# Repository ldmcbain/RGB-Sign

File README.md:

# RGB Sign
 RGB Wifi Sign Controller using ESP32-DevkitC-32E

This is an RGB Sign I created for our church.  It is an Arduino based design using a custom PCB I created to conrol three separate RGB strings.  I created the PCB using a two-sided copper board and a laser burner, but someone could just as easily send it out for build.

The Arduino is setup to create a WIFI captive portal which is used to control the three strands. Update the wifi settings in the arduino code prior to use.

Note that the PCB uses the ESP32-DevkitC-32E layout.  Other ESP32 variations may have incorrect dimensions or pinouts.

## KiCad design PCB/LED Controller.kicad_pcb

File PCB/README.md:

This PCB was created in KiCad v5.1.10

I generated the PCB using a standard 5W laser.  Here are my steps to do so if you are so inclined:

Like all things, follow these steps at your own risk.  This process involves toxic chemicals, soldering, etc and you must follow proper safety precautions if attempting.  If you are not comfortable with the equipment/process, don't do it.

**KiCad Design**
  Min Trace Width: 0.4mm
  Min Clearance: 0.25mm
  All Vias should be 2.5mm diameter and not placed under anything
  Use a ground flood plane on most surfaces (reduces required lasering)
  
**From within PCBNew**
  Plot out Top/Bottom Cu layers to PDF.  Utilize small drill holes, show cut edge on all layers
  
**Using GIMP**
1. Import PDF as high res (2400 dpi)
2. Auto Crop to content
3. Modify to fill in the outer edge so that it is all black (don't laser the edges)
4. Export as high res PNG

**Prepare the Board**
1. (optional) Sand the board lightly with 400 grit
2. Spray paint the board (both sides).  Make sure fully coated.  I used the cheap matte black spray at walmart.  Use two coats if needed.

**Lightburn Laser Control SW**
1. Import PNG into lightburn
2. Use Following settings for laser (this is what worked for me, modify as needed)
  a. 60% power
  b. speed: 3mm/s
  c. Bi-directional: Off
  d. Negative Image: On
  e. Overscanning: Off
  f. Line Interval: 0.1mm
  g. Passes: 1

**Burning and Post Clean up/Fabrication**
1. Position and Burn the Board (one side at a time..).  Note: you should be burning a Negative image on the board (areas in-between the copper).
2. Clean up board with scotch bright pad (and water).  Use a ultra fine tip marker to fix damaged areas if needed.
3. After both sides are burned, etch the board using ferric chloride solution.  This can be obtained from amazon.  USE GLOVES!!  There are several youtube videos showing how to do this if you are unfamiliar with the process.
4. Clean the board with water.  Inspect and re-etch if needed.
5. Use acetone or paint thinner to remove remaining paint from the board.
6. Clean board with alcohol (i use the 90% stuff at walmart)
7. Drill the holes.  I obtained very small drills from amazon for the purpose and used a drill press.  Use 0.8mm dia for vias.  They *should* be marked with small dots.  use the drill map to make sure you get all of them with the right size drills.
8. In some instances, I've found it helpful to pre-tin the board in certain locations.
9. Assemble the board.

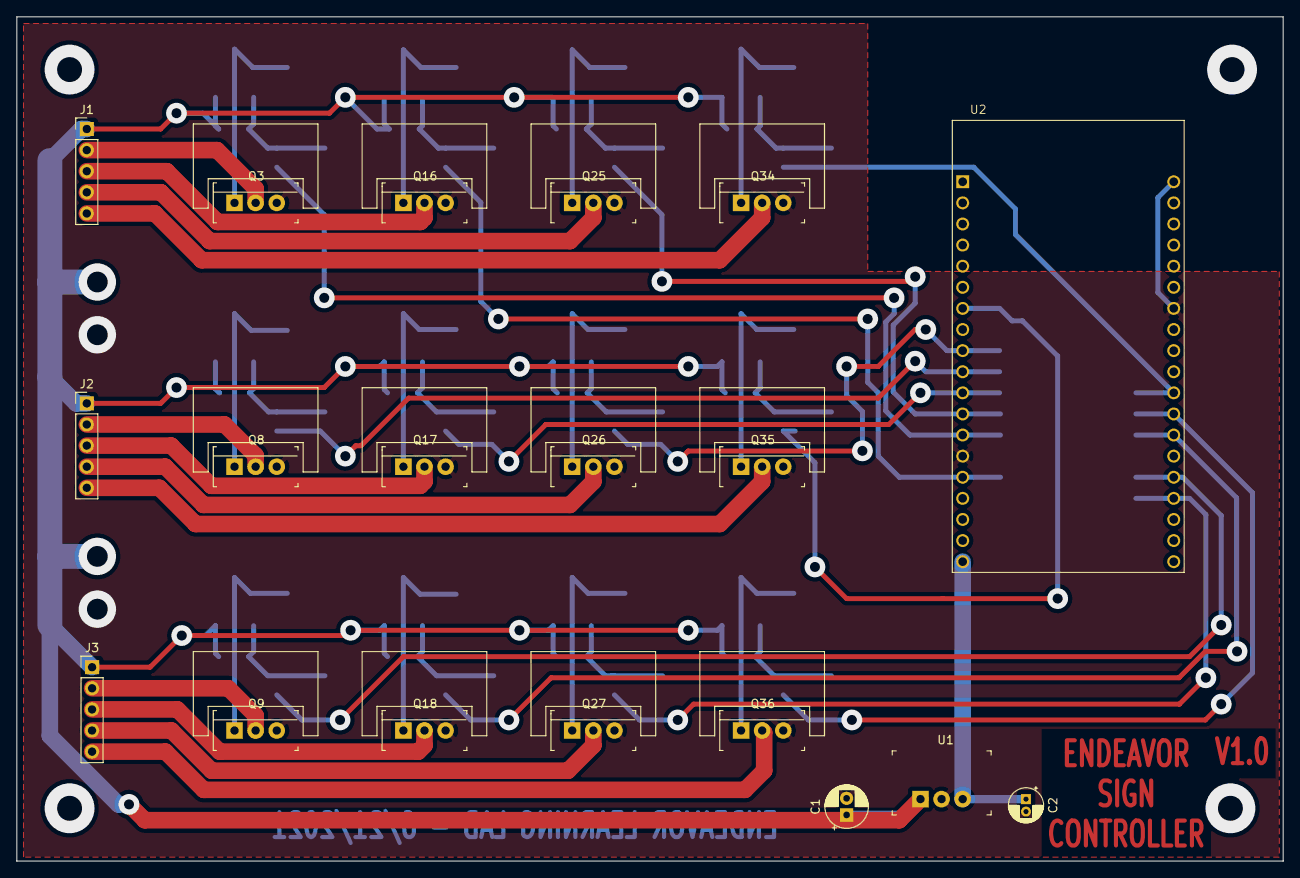
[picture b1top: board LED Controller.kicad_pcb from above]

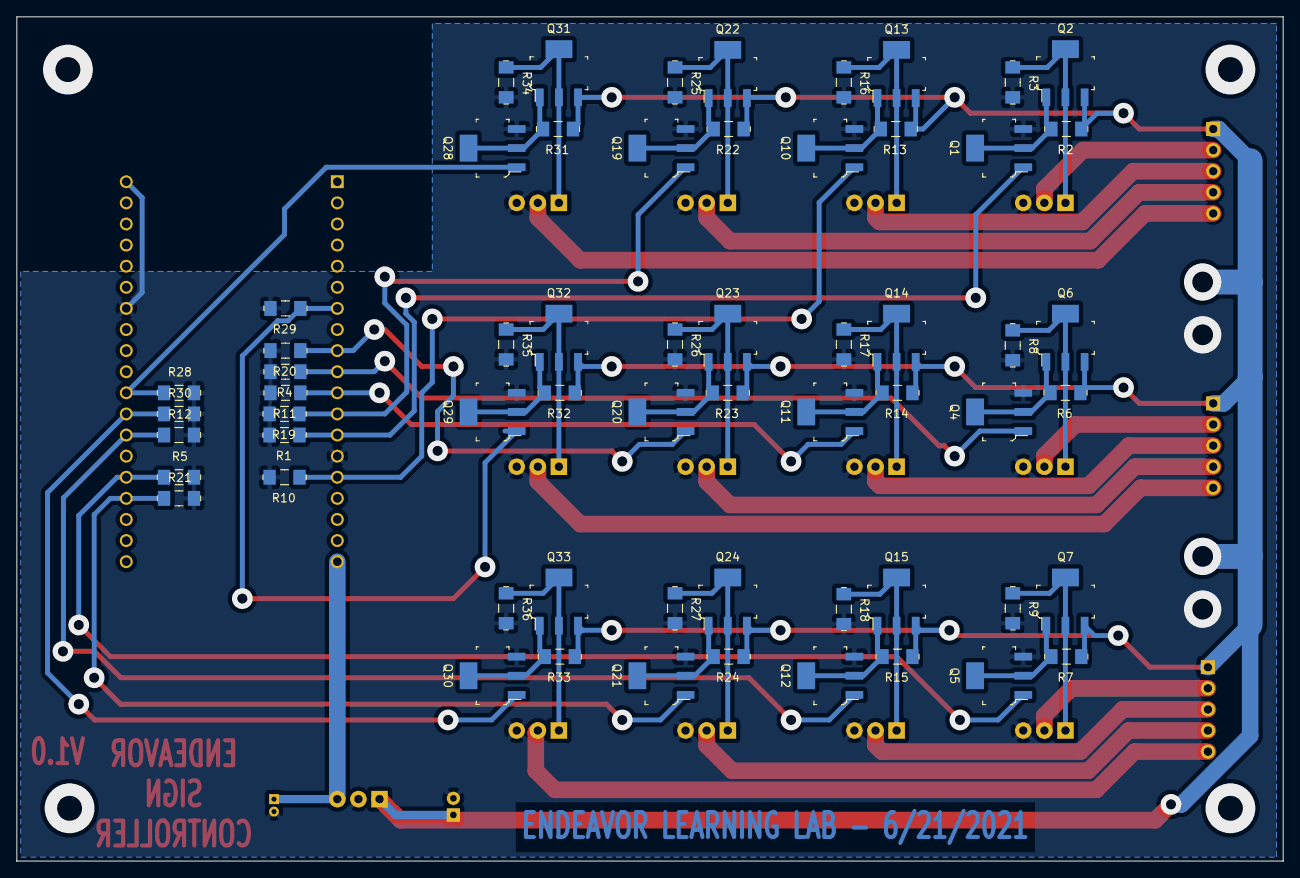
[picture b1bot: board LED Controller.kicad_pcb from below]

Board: 2 copper layers, 152.4 x 101.6 mm, 79 parts (60 on the bottom side), 51 nets.

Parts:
C1: 10u; CP_Radial_D5.0mm_P2.00mm
C2: 22u; CP_Radial_D4.0mm_P1.50mm
J1, J2, J3: Conn_01x05; PinHeader_1x05_P2.54mm_Vertical
Q1, Q4, Q5, Q10, Q11, Q12, Q19, Q20, Q21, Q28, Q29, Q30: Q_NMOS_GDSD; SOT-223-4
Q2, Q6, Q7, Q13, Q14, Q15, Q22, Q23, Q24, Q31, Q32, Q33: Q_PMOS_GDSD; SOT-223-4
Q3, Q8, Q9, Q16, Q17, Q18, Q25, Q26, Q27, Q34, Q35, Q36: Q_NMOS_GDS; TO-220-3_Heatsink
R1, R2, R3, R4, R5, R6, R7, R8, R9, R10, R11, R12, R13, R14, R15, R16, R17, R18, R19, R20, R21, R22, R23, R24, R25, R26, R27, R28, R29, R30, R31, R32, R33, R34, R35, R36: 10k; 1206
U1: V7805-500; 3-SIP_Module_V7805-500
U2: ESP32-DEVKITC-32D; MODULE_ESP32-DEVKITC-32D

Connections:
5V: C2.1, U1.3, U2.19
+24V: C1.1, J1.1, J2.1, J3.1, Q2.3, Q6.3, Q7.3, Q13.3, Q14.3, Q15.3, Q22.3, Q23.3, Q24.3, Q31.3, Q32.3, Q33.3, R2.1, R6.1, R7.1, R13.1, R14.1, R15.1, R22.1, R23.1, R24.1, R31.1, R32.1, R33.1, U1.1
B_1: Q19.1, R19.1, U2.12
B_2: Q20.1, R20.1, U2.9
B_3: Q21.1, R21.1, U2.35
GND: C1.2, C2.2, Q1.3, Q3.3, Q4.3, Q5.3, Q8.3, Q9.3, Q10.3, Q11.3, Q12.3, Q16.3, Q17.3, Q18.3, Q19.3, Q20.3, Q21.3, Q25.3, Q26.3, Q27.3, Q28.3, Q29.3, Q30.3, Q34.3, Q35.3, Q36.3, R1.2, R3.2, R4.2, R5.2, R8.2, R9.2, R10.2, R11.2, R12.2, R16.2, R17.2, R18.2, R19.2, R20.2, R21.2, R25.2, R26.2, R27.2, R28.2, R29.2, R30.2, R34.2, R35.2, R36.2, U1.2, U2.14, U2.20, U2.26
G_1: Q1.1, R1.1, U2.13
G_2: Q4.1, R4.1, U2.10
G_3: Q5.1, R5.1, U2.34
unnamed: J1.2, Q3.2
unnamed: J1.3, Q16.2
unnamed: J1.4, Q25.2
unnamed: J1.5, Q34.2
unnamed: J2.2, Q8.2
unnamed: J2.3, Q17.2
unnamed: J2.4, Q26.2
unnamed: J2.5, Q35.2
unnamed: J3.2, Q9.2
unnamed: J3.3, Q18.2
unnamed: J3.4, Q27.2
unnamed: J3.5, Q36.2
unnamed: Q1.2, Q1.4, Q2.1, R2.2
unnamed: Q2.2, Q2.4, Q3.1, R3.1
unnamed: Q4.2, Q4.4, Q6.1, R6.2
unnamed: Q5.2, Q5.4, Q7.1, R7.2
unnamed: Q6.2, Q6.4, Q8.1, R8.1
unnamed: Q7.2, Q7.4, Q9.1, R9.1
unnamed: Q10.2, Q10.4, Q13.1, R13.2
unnamed: Q11.2, Q11.4, Q14.1, R14.2
unnamed: Q12.2, Q12.4, Q15.1, R15.2
unnamed: Q13.2, Q13.4, Q16.1, R16.1
unnamed: Q14.2, Q14.4, Q17.1, R17.1
unnamed: Q15.2, Q15.4, Q18.1, R18.1
unnamed: Q19.2, Q19.4, Q22.1, R22.2
unnamed: Q20.2, Q20.4, Q23.1, R23.2
unnamed: Q21.2, Q21.4, Q24.1, R24.2
unnamed: Q22.2, Q22.4, Q25.1, R25.1
unnamed: Q23.2, Q23.4, Q26.1, R26.1
unnamed: Q24.2, Q24.4, Q27.1, R27.1
unnamed: Q28.2, Q28.4, Q31.1, R31.2
unnamed: Q29.2, Q29.4, Q32.1, R32.2
unnamed: Q30.2, Q30.4, Q33.1, R33.2
unnamed: Q31.2, Q31.4, Q34.1, R34.1
unnamed: Q32.2, Q32.4, Q35.1, R35.1
unnamed: Q33.2, Q33.4, Q36.1, R36.1
R_1: Q10.1, R10.1, U2.15
R_2: Q11.1, R11.1, U2.11
R_3: Q12.1, R12.1, U2.32
W_1: Q28.1, R28.1, U2.30
W_2: Q29.1, R29.1, U2.7
W_3: Q30.1, R30.1, U2.31

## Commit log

2021-12-30 Upload
2021-12-30 Added Photo
2021-12-30 added photos
